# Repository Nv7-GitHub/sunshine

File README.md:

# Sunshine Combat Robot
This is the code for a 1lb melty-brain combat robot. This is a combat robot whose body spins and the wheel speeds are modulated while spinning for translation. There are 3 main components to this robot:

- Robot brain (sunshine_brain): ESP32-S3, which reads the sensors, does the processing, and sends the telemetry via ESP-now to the receiver and receives motion commands and safety-related commands (e.g. enable, disable, etc.)
- Receiver (sunshine_receiver): ESP32-S3, which receives the telemetry and sends it to the host app as well as sends out telemetry commands from the host app
- Host app (sunshine_app): Graphs data, displays telemetry, saves logs to files, handles replay (has to interact with sunshine_brain code for this) and simulation

## Tech stack
All embedded code will be implemented via platform IO. The host app code will be Tauri with React for the frontend. For replay (explained below), the brain code that is above the IO layer has to be very encapsulated so that it can be called from the Tauri rust code.

## Replay
The core concept of this project is IO layers and replay. The core sensors: **time (precise)**, wheel eRPM, ESP-NOW RSSI, magnetometer reading, battery voltage, control inputs from the driver, and accelerometer readings are all sampled at 1kHz and logged via telemetry. 

All the brain code processes these inputs (which are below the IO layer) and runs code that affects the **state**. The state is every variable that changes over time as a result of previous inputs. This should just be the external and internal states of any filters being used. 

The telemetry packets are sent out at 50 Hz, so each packet should include two state snapshots — one at the start of the packet and one at its midpoint (the 10th of its 20 samples), giving the real state at 100 Hz — and then the 20 IO layer samples that happened since the start state. The two states let the host both initialize the filters and double-check the replay against the real state twice per packet. This will minimize data usage because the host app can simply receive the state to initialize the filters and then run replay from there on. In the log files, the real state is likewise logged at 100 Hz (two snapshots per 50 Hz frame; theoretically you could even do it once but I want to be able to always have something to double-check the replay against and/or a way to handle changed code since you collected the telemetry) and the data below the IO layer is logged at the full 1kHz. Variables are NOT logged — they are a pure function of state + inputs, so the host always recomputes them (both the real and replayed versions).

The replay should use the ACTUAL robot code and just feed it a different source of IO layers instead of the raw sensors. So if you make a code change, you could re-run the code using the logged telemetry data and see if it fixes a bug that is occurring, for example.

This IO layer concept is important because it lets you implement simulation, where instead of having the receiver managing state you just implement a basic simulation of the motors and how it affects the sensors in an ideal world and then you can simulate the robot fully on the computer, once again just feeding the simulated sensor data into the IO layer.

In addition to the **state** and **inputs** (data below the IO layer) you also have the **variables** - data that is calculated from the state or inputs without any historical components. This is also logged at 50 Hz, but never sent over telemetry, just logged by the host app. This is once again so that if code changes occur you don't lose the data that was produced by the old code, which is necessary for determining if changes actually led to fixes. 

Replay is designed with AI assistance in mind. Develop Claude skills to aid with debugging code with validation via replay and simulation in parallel to this. Design everything with debugging and ugpradeability in mind. Changing what's in the state, what the inputs are, etc. should be easy and backwards-compatible (so old log data should still be usable). Adding a new variable (especially to the state and variables, which I anticipate changing a lot) should be very easy and well documented for future AI sessions along with the codebase in general.

## Robot brain

The robot brain has the two components mentioned before: below the IO layer, and above the IO layer. Everything above the IO layer has to be able to be run both on the host computer as well as the robot, so it should never interact with hardware directly and should be able to easily be compiled and run on a variety of host computer platforms. For below the IO layer, here is the hardware map:

## Hardware map
IMU is an ADXL375, 11mm from the center of the robot (this is important for calculating ang vel from the centripetal accel). The IMU is rotated 45 degrees so it saturates less.
- IO8: IMU_INT1
- IO9: IMU_INT2
- IO10: IMU_CS
- IO11: IMU_MOSI
- IO12: IMU_SCK
- IO13: IMU_MISO

Mag is LIS3MDL
- IO14: MAG_DRDY
- IO15: MAG_MOSI
- IO16: MAG_SCK
- IO17: MAG_MISO
- IO18: MAG_CS
- IO21: MAG_INT

There is an LED connected to IO38 that can be PWMed. It's connected to the gate of a low side switch so you drive it high to turn on the LEDs.

IO7 is connected with a voltage divider (2kohm high, one kohm low) to the battery positive terminal

IO4 is the signal pin of the left wheel ESC (S1), IO5 is for the right wheel ESC (S2). Use bidirectional DShot 600.

USB is connected, so you can use USB for debugging info

## Core splitting
There are 3 overall tasks running on the brain: telemetry, navigation, and control. 

### Telemetry
Telemetry should be running on the ESP32 core that is meant for telemetry. The data is getting sent out at a fixed 50 Hz and should be received from the transmitter at 500 Hz. This core should receive state (the history, or maybe it buffers the history itself but as explained earlier in each packet there's the state and then the 50 subsequent inputs). This core also uses the RSSI from the receiver and sends it over to the control core as this is one of the inputs. The receiver and transmitter should be configured to send at the absolute max strength, and the transmitter should be sending without waiting for acknowledgement or anything. For the telemetry it should be robust since any missing data will mess up replay, so determine a protocol that is able to do that without causing congestion so the packets with RSSI and control inputs can be sent at the 500 Hz. This is in a very RF noisy environment so account for that appropriately.

IMPORTANT: When the robot is disabled in the host app, it HAS to disable in real life. This is a strict requirement as it is critical to safety.

### Navigation
Navigation is the 1kHz sensor read and filter update loop. All the sensors can be read at 1kHz or faster (make sure to configure correctly) and all are connected via SPI so it should be fast. The filter is as follows:
- The accelerometer data is used to determine angular velocity. When being transmitted, this is an int16
- The magnetometer data goes through a butterworth filter with a cutoff roughly in the range of what Earth's magnetic field should be oscillating at. Calculate the minimum speed needed before zero DC leaks through and set that as the minimum speed to use this sensor, as there will be a lot of DC offset due to current draw from the ESC and various metallic objects. The raw reading is also an int16 for telemetry. The filter will be part of the state (and needs appropriate history). 
- The wheel ERPM is not going to be used for anything navigation-related. However, it can be used for torque-limiting and for looking at things like wheel slip in the logged data after. Log this as a float16.
- The RSSI is from the actual ESP-NOW receiving data. This is an int8. This is eventually going to be worked into the filter but I think the shape of it's curve depends on antenna stuff so I will collect some data not using it initially and try to analyze it before incorporating it into anything. 
- The host computer sends x, y, theta, and throttle. X/Y/Theta are all int8 and throttle is uint8. 
- The battery voltage can be represented as a int8, relative to 7.6V (the robot is 2S). The range needs to go to 5.0V and be symmetrical.
- Put the applied DShot signals into the inputs too, but quantize down to uint8 for each since I just want to see the overall shape at 1kHz, it is never going to be used anywhere.
- Time should be of the necessary precision to be accurate down to a decimal OF the control loop (so since the loop is at 1kHz, it should be accurate to ten-thousandths of a second) which means a uint32 is needed.

Make sure to consider endian-ness correctly for telemetry or use some protocol.

The overall Kalman filter will use the magnetometer as an absolute reference (since with the DC filtered out from the butterworth it should actually represent absolute position), the accelerometer gives velocity for the kalman filter, and eventually the RSSI will either give velocity or position but that is to be determined. 

The theta control defines an offset from the absolute position from the magnetometer. That way the driver can rotate the zero heading reference. 

The kalman filter will need to be tuned somewhat. Develop necessary code (this will probably happen during bringup) and include instructions to tune it. 

### Control
Control also happens in the same 1kHz loop. It is CRITICAL that this tight 1kHz loop does not overrun, and I should know about it when it is happening. The inputs include precise time so the host app should be receiving this, and of course loop overruns should be included in the USB output along with any initialization errors for the sensors. Make sure to have a distinct LED pattern if there are initialization errors too with the sensors, since usually I won't have USB connected during init so I would connect USB once I see that pattern (so the error should be continuously printed). 

During control, the LED has to be turned on from -3 deg to +3 deg (of course relative to the driver-controlled zero heading). 

The X and Y controls will be used for translational control. For the translational drift, use triangle waves in a portion of the rotation such that it can drive. The amplitude of the wave should depend on the magnitude of the X/Y control. Write a document on how to tune this (what to change and how that will affect the motion and what I should look for). I am thinking of a triangle wave instead of the usual square because the melty should be traction limited and a triangle wave should limit slip. Maybe a trapezoidal wave instead of a triangle if that would be more optimal.

There are two modes of control. There is DISABLED, which is critical to safety and the host app will control this. Then there is TANK, where the robot is driven around like a traditional robot, so throttle controls forwards backwards and the x control (side-to-side) should determine turning. Y and theta are unused. Finally, there is MELTY where throttle controls target angular speed (for now open-loop), X is for side-to-side, Y is forwards backwards, and theta controls the offset. This is holonomic unlike the previous tank drive mode so you can of course mix the X and Y. In the app design mockup (included below) there is only ENABLED and DISABLED so this needs to be changed to have DISABLED, TANK, MELTY.

## Bringup
There is no way that the entire codebase can be put onto the device and everything will work, so bringup needs to occur where each specific function has to be individually tested. Design a clean way of doing this. Here are the levels of bringup:
1. Low-level sensors: Read the accelerometer, plot via USB, make sure that works, same for the magnetometer, voltage sensor. etc.
2. Low-level control: Test the bidirectional DShot and make sure everything spins up correctly
3. Telemetry link: Test the ESP-NOW connection between the brain and the receiver, including sending the inputs and receiving the RSSI data. At this point the host app has to get in the loop too, and I should be able to plot accel, rssi, etc.
4. Navigation tuning: The kalman filter and other parameters must be tuned so that the device can localize well. At this point I will use the tank mode to spin the robot, MELTY mode will still not be used.
5. Drift tuning: MELTY mode is finally enabled, heading control should be good (so the LED should be solid and still), and I can tune the drift profile

Make sure it is an easy process and write instructions.

# Receiver
The receiver is simply the other side of the link from the robot brain. It should receive the necessary info and send it via USB (it is an ESP32-S3 so should have plenty of bandwidth) to the host app and send data. The accompanying protocols must be developed. 

# Host app
The UI mockup has been made:

## UI Mockup
Fetch this design file, read its readme, and implement the relevant aspects of the design. https://api.anthropic.com/v1/design/h/ER_Esv7z8Q_IkM8_wpP-5Q?open_file=Sunshine+Dashboard.html
Implement: Sunshine Dashboard.html

Note that this mockup has some unnecesary info plotted on top (e.g. CPU usage doesn't make sense, but seeing the bandwidth over the connection or the RSSI would be useful up there), and the variables are fully made up. Instead of ENABLE DISABLE there should be DISABLE, TANK, MELTY. In addition to x-y and throttle there is also the theta control. The current keybinds are:
W/S for Y, A/D for X, left/right arrow for theta, and up/down arrow for throttle (where throttle adds up instead of being like when you let go it goes to zero). This should be HEAVILY low-pass filtered (even more than the current mockup) so that I can basically emulate having a controller by pulsing WASD and the left/right arrow keys.

The connections section of the UI doesn't make sense. Robot is 2S so of course adjust battery indicator colors accordingly. Get rid of the E-STOP button as that's the same as DISABLE. Inputs menu is unneeded. Retain the same graph controls but fix it because right now it's a little jerky and awkward (way too sensitive to the scroll). 

You should be able to do replay, simulation, and connect to the real robot through the UI. Implement that stuff into where the "CONNECTIONS" area is currently. For replay you would pick a log file, simulation just spins up a simulation, and connecting to the robot would connect to the receiver and then look at whether the receiver is connected and all. Error handling will need to be coordinated across all devices in the chain in a robust and extendable manner.

## Logging
The code needs to log a decent amount of data at 50 Hz (where each 50 Hz frame has those 20 inputs). Use binary so the file is small and of course design around the backwards compatibility aspect so that old files can be used with versions of the software that have new variables.

## Plotting
You should be able to plot both the actual 50 Hz data as well as your replayed data for the state variables (this applies when connected to the real robot as well as when replaying from a data file, in simulation it doesn't really make sense but they can probably just be the same thing but one is at 50 Hz). The only reason we replay even when connected to the real robot is so that we can see what's going on at 1kHz, so the replayed data should look like a high-resolution version of the 50 Hz data. Make sure to design the graphing UI such that it can handle the high density of points / quantize since of course rendering at 1kHz when you are showing a minute of data would probably cause lag issues, so consider that when implementing the graphing. 

## Inputs, State, and Variables
All things being plotted have their own units. You can already see this system well implemented in the mockup.

The inputs should all be plotted under the inputs dropdown. Most of the state (e.g. the kalman filter internal covariances, butterworth history) don't make sense to plot so only things like position, velocity, and the magnetometer data after the filter really make sense to plot.

Even though the control outputs are logged at 1kHz as part of the inputs, they will get re-calculated during replay and so there should be a way of viewing the new control outputs too. That's why even though during telemetry they are part of the inputs in the app graphing they should be part of the STATE since they have separate values received vs replayed. We basically have a Real State and a Replayed State which of course includes the 50 Hz things above but also the 1kHz wheel applied values.

The variables are only present in the replayed values, as they are never sent from the robot. Think of all important values. e.g. velocity calculated from the accelerometer would be a variable that should be plotted. All possibly useful info should be plottable.

The app has to call the actual C code to emulate the control and state estimation. This will require calling of C code from Rust. 

## Simulation
Use the basic electrical model of a brushed motor. (Back-EMF source, resistance, etc.). The KV of the motors is 1100KV (this should be an easily editable constant though). I don't know the exact resistance but lets say each phase is 75mohm. The battery is a 2S 650mah 120C LiPo. Don't model battery draining but model internal resistance using like the supply current derived from the stator current in the motor, pick a reasonable internal resistance for a battery with these specs. For the magnetomer, just do ideal earth's magnetic field, same for accelerometer. here are some more physical parameters you need:
- Wheel Diameter: 44mm
- The wheels are 81mm apart (so radius from center is 40.5mm). 
- The MoI of the robot is 1213859.17531 g-mm^2
- Wheel MoI is 6407.44019 g-mm^2
Use metric for everything.

I believe the max body RPM is somewhere around 4,000, you should double check this to ensure I gave you the right-specs.

# General Notes
Everything should be implemented robustly. If everything is connected and setup but then I unplug and replug the receiver, the host app should handle that gracefully and make a new log file. There also should be an easy way to disable logging from the host app. If the robot momentarily loses power or disconnects and then reconnects the host app and receiver should handle this gracefully. The disabled aspect is critical to safety. The code should be very well documented (in MD files) such that future AI sessions can read an info document and know what files to edit. There should be instructions for tuning meant for humans. Also make it easy to label log files (e.g. during comp it should be based on match, but always include date and stuff)

IMPLEMENT SKILLS TO AID WITH DEBUGGING!

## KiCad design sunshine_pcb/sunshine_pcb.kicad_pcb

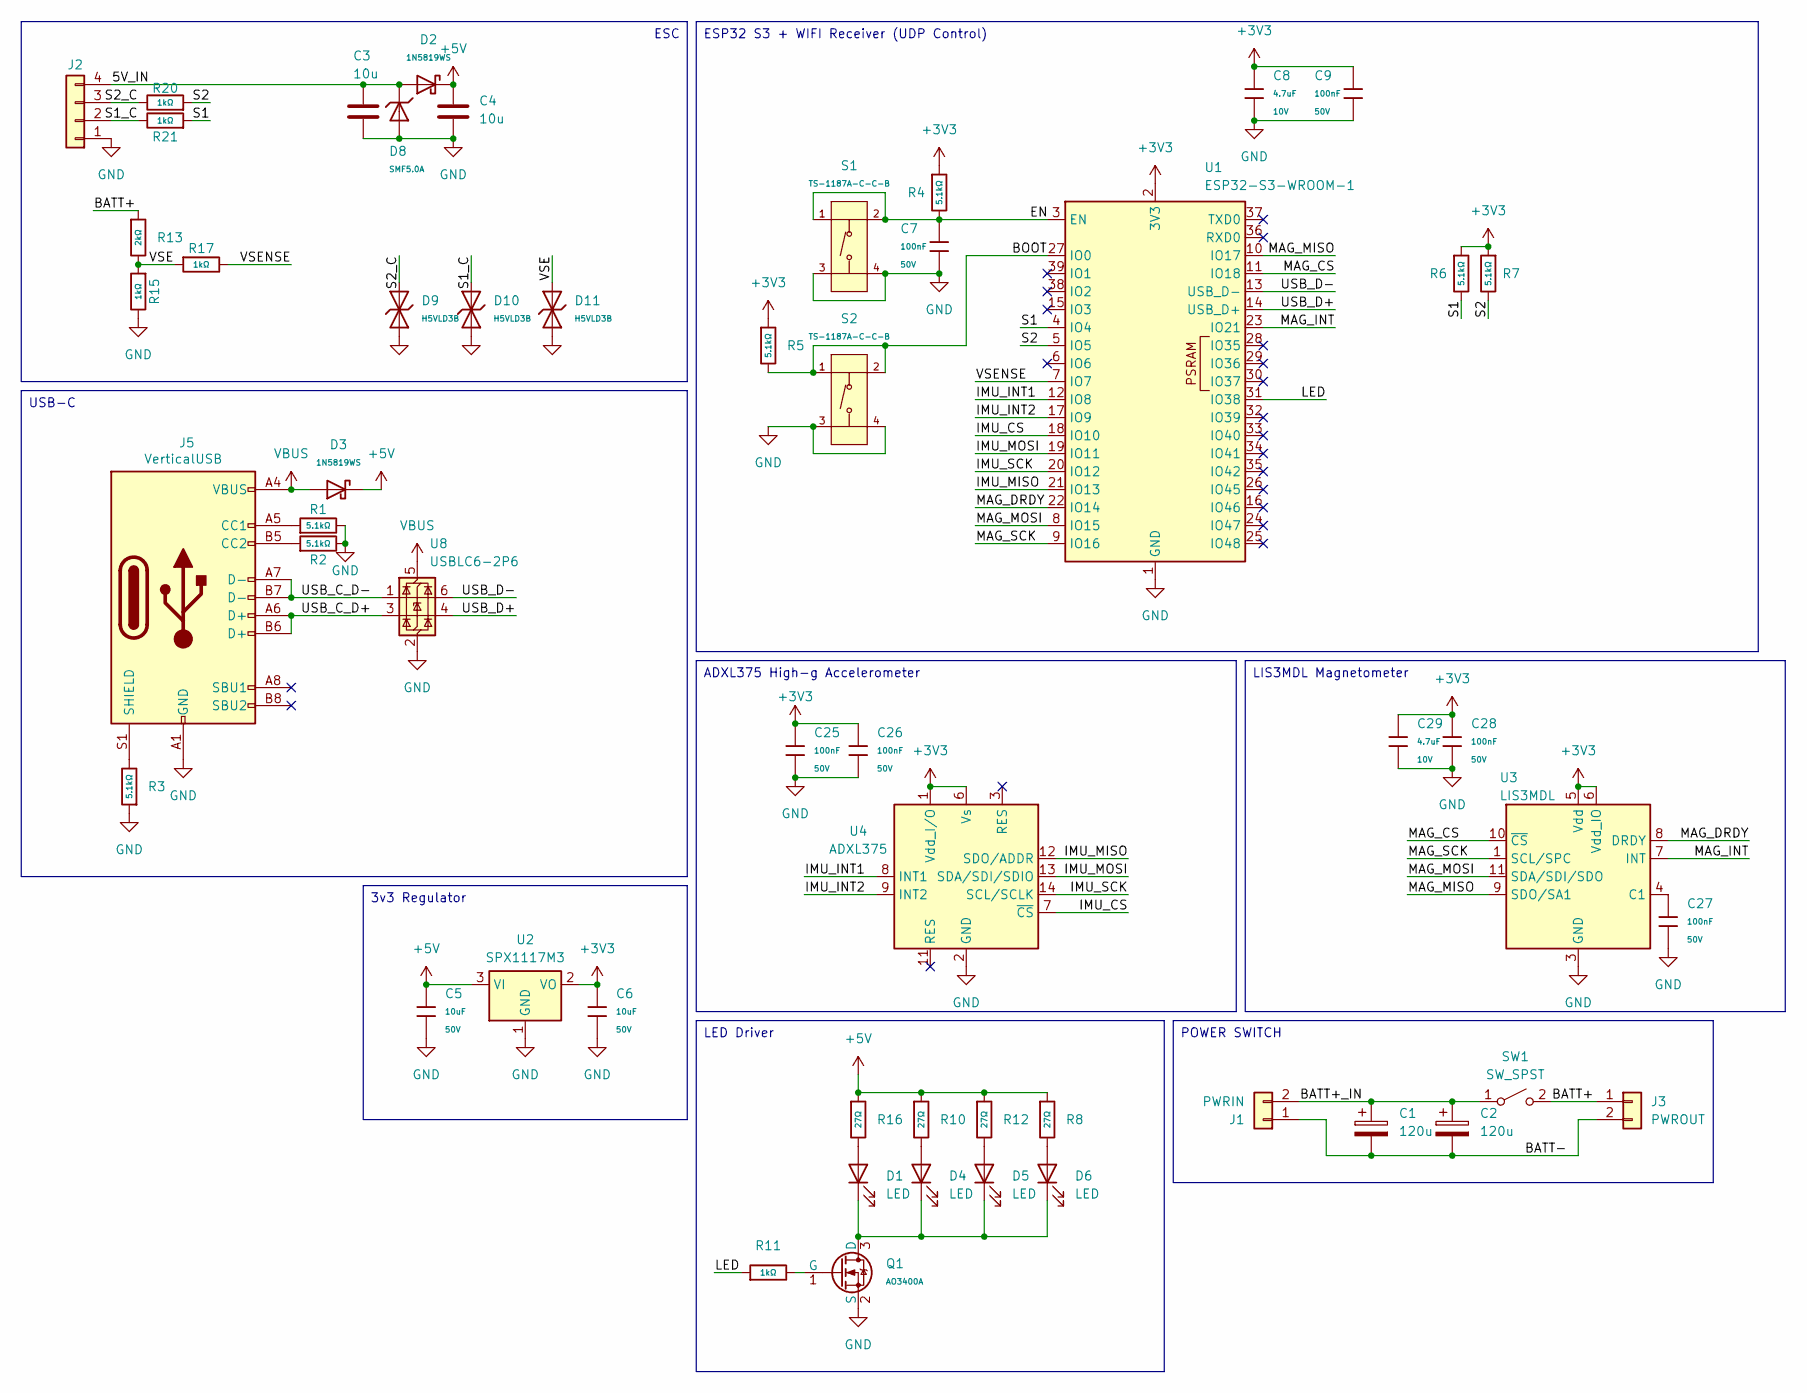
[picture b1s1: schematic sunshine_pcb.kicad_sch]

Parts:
C1, C2: 120u; CP_Radial_D6.3mm_P2.50mm
C3, C4: 10u; C_1210_3225Metric; LCSC C437431
C5, C6: 10uF; C_0805; Voltage Rated 50V; Tolerance ±10%; Part GRM21BR61H106KE43L; LCSC C440198
C7, C9, C25, C26, C27, C28: 100nF; C_0402; Voltage Rated 50V; Tolerance ±10%; Part CL05B104KB54PNC; LCSC C307331
C8, C29: 4.7uF; C_0402; Voltage Rated 10V; Tolerance ±20%; Part CL05A475MP5NRNC; LCSC C23733
D1, D4, D5, D6: LED; LED_PLCC_2835; LCSC C2843876
D2, D3: 1N5819WS; D_SOD-323; Forward Voltage (Vf@If) 600mV@1A; Reverse Voltage (Vr) 40V; Part 1N5819WS; LCSC C191023
D8: SMF5.0A; D_SOD-123FL; Part SMF5.0A; LCSC C19077497
D9, D10, D11: H5VLD3B; D_SOD-323; Part H5VLD3B; LCSC C20615805
J1: PWRIN; AMASS_XT30PW-M_1x02_P2.50mm_Horizontal
J2: Conn_01x04; SolderConnector4P; LCSC C122413
J3: PWROUT; SolderWire-1.5sqmm_1x02_P6mm_D1.7mm_OD3mm
J5: VerticalUSB; CONN_GT-USB-7055A_GSW
Q1: AO3400A; Q_SOT-23; Part AO3400A; LCSC C20917
R1, R2, R3, R4, R5, R6, R7: 5.1kΩ; R_0402; Overload Voltage (Max) 50V; Tolerance ±1%; Part 0402WGF5101TCE; LCSC C25905
R8, R10, R12, R16: 27Ω; R_0805; Overload Voltage (Max) 150V; Tolerance ±1%; Part 0805W8F270JT5E; LCSC C17594
R11, R15, R17, R20, R21: 1kΩ; R_0402; Overload Voltage (Max) 50V; Tolerance ±1%; Part 0402WGF1001TCE; LCSC C11702
R13: 2kΩ; R_0402; Overload Voltage (Max) 50V; Tolerance ±1%; Part 0402WGF2001TCE; LCSC C4109
S1, S2: TS-1187A-C-C-B; SW-SMD_4P-L5.1-W5.1-P3.70-LS6.5-TL-2; Voltage Rating (Dc) 12V; Part TS-1187A-B-A-B; LCSC C318889
SW1: SW_SPST; screw_switch
U1: ESP32-S3-WROOM-1; LCSC C2913202
U2: SPX1117M3; SOT-223-3_TabPin2; LCSC C6862
U3: LIS3MDL; LGA-12_2x2mm_P0.5mm; LCSC C478483
U4: ADXL375; LGA-14_3x5mm_P0.8mm_LayoutBorder1x6y; LCSC C481898
U8: USBLC6-2P6; SOT-666; LCSC C15999

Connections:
+3V3: C6.1, C8.1, C9.1, C25.1, C26.1, C28.1, C29.1, R4.1, R5.1, R6.1, R7.1, U1.2 (3V3), U2.2 (VO), U3.5 (Vdd), U3.6 (Vdd_IO), U4.1 (Vdd_I/O), U4.6 (Vs)
+5V: C4.1, C5.1, D2.1, D3.1, R8.1, R10.1, R12.1, R16.1, U2.3 (VI)
/5V_IN: C3.1, D2.2, D8.1, J2.4
/BATT+: J3.1, R13.1, SW1.2 (B)
/BATT+_IN: C1.1, C2.1, J1.2, SW1.1 (A)
/BATT-: C1.2, C2.2, J1.1, J3.2
/BOOT: R5.2, S2.1 (A), S2.2 (B), U1.27 (IO0)
/EN: C7.1, R4.2, S1.1 (A), S1.2 (B), U1.3 (EN)
/IMU_CS: U1.18 (IO10), U4.7 (~CS)
/IMU_INT1: U1.12 (IO8), U4.8 (INT1)
/IMU_INT2: U1.17 (IO9), U4.9 (INT2)
/IMU_MISO: U1.21 (IO13), U4.12 (SDO/ADDR)
/IMU_MOSI: U1.19 (IO11), U4.13 (SDA/SDI/SDIO)
/IMU_SCK: U1.20 (IO12), U4.14 (SCL/SCLK)
/LED: R11.1, U1.31 (IO38)
/MAG_CS: U1.11 (IO18), U3.10 (~CS)
/MAG_DRDY: U1.22 (IO14), U3.8 (DRDY)
/MAG_INT: U1.23 (IO21), U3.7 (INT)
/MAG_MISO: U1.10 (IO17), U3.9 (SDO/SA1)
/MAG_MOSI: U1.8 (IO15), U3.11 (SDA/SDI/SDO)
/MAG_SCK: U1.9 (IO16), U3.1 (SCL/SPC)
/S1: R6.2, R21.1, U1.4 (IO4)
/S1_C: D10.2, J2.2, R21.2
/S2: R7.2, R20.1, U1.5 (IO5)
/S2_C: D9.2, J2.3, R20.2
/USB_C_D+: J5.A6 (D+), J5.B6 (D+), U8.3 (I/O2)
/USB_C_D-: J5.A7 (D-), J5.B7 (D-), U8.1 (I/O1)
/USB_D+: U1.14 (USB_D+), U8.4 (I/O2)
/USB_D-: U1.13 (USB_D-), U8.6 (I/O1)
/VSE: D11.2, R13.2, R15.1, R17.1
/VSENSE: R17.2, U1.7 (IO7)
GND: C3.2, C4.2, C5.2, C6.2, C7.2, C8.2, C9.2, C25.2, C26.2, C27.2, C28.2, C29.2, D8.2, D9.1, D10.1, D11.1, J2.1, J5.A1 (GND), J5.A12 (GND), J5.B1 (GND), J5.B12 (GND), Q1.2 (S), R1.2, R2.2, R3.1, R15.2, S1.3 (C), S1.4 (D), S2.3 (C), S2.4 (D), U1.1 (GND), U1.40 (GND), U1.41 (GND), U2.1 (GND), U3.2 (GND), U3.3 (GND), U3.12 (GND), U4.2 (GND), U4.4 (GND), U4.5 (GND), U8.2 (GND)
unnamed: D1.2 (A), R16.2
unnamed: D1.1 (K), D4.1 (K), D5.1 (K), D6.1 (K), Q1.3 (D)
unnamed: D4.2 (A), R10.2
unnamed: D5.2 (A), R12.2
unnamed: D6.2 (A), R8.2
unnamed: J5.A5 (CC1), R1.1
unnamed: J5.B5 (CC2), R2.1
unnamed: J5.S1 (SHIELD), R3.2
unnamed: Q1.1 (G), R11.2
unnamed: C27.1, U3.4 (C1)
VBUS: D3.2, J5.A4 (VBUS), J5.A9 (VBUS), J5.B4 (VBUS), J5.B9 (VBUS), U8.5 (VBUS)

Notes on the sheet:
ADXL375 High-g Accelerometer
ESC
LIS3MDL Magnetometer
LED Driver
3v3 Regulator
POWER SWITCH
USB-C
ESP32 S3 + WIFI Receiver (UDP Control)

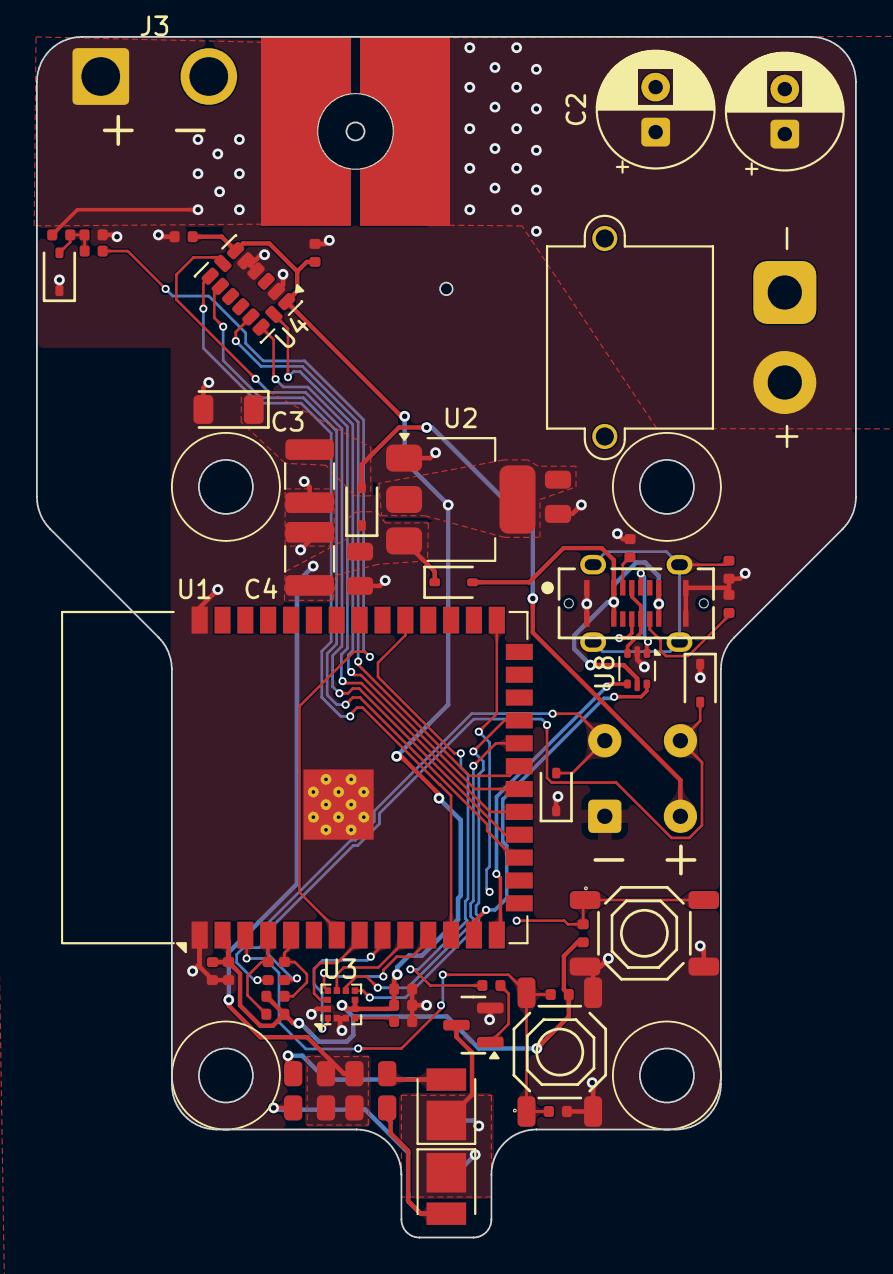
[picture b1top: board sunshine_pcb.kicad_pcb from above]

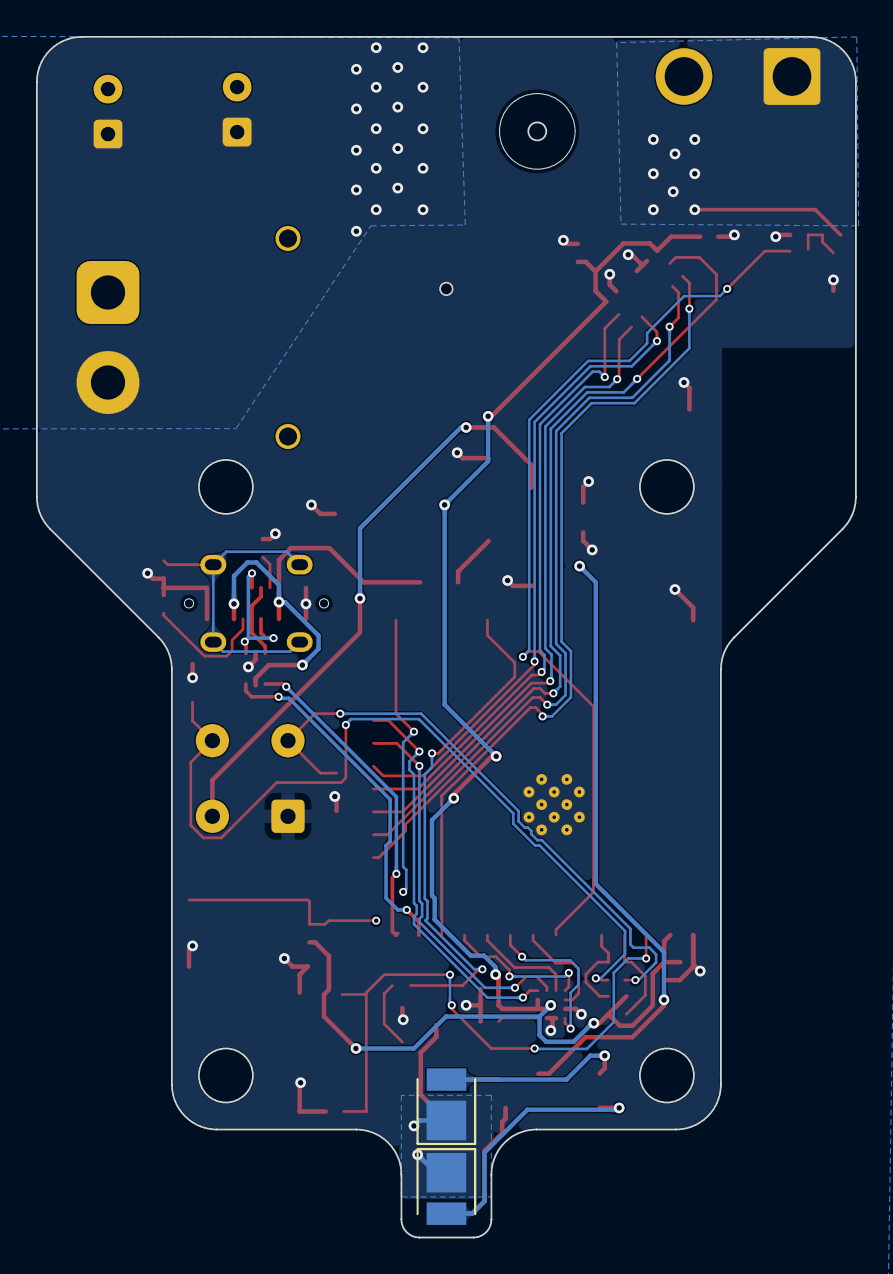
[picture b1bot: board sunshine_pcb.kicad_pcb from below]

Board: 4 copper layers, 45.5 x 66.7 mm, 54 parts (2 on the bottom side), 43 nets.

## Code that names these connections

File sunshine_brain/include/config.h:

#pragma once
#include <stdint.h>

// ── SPI pins
// ────────────────────────────────────────────────────────────────── FSPI →
// ADXL375
#define PIN_ADXL_CS 10
#define PIN_ADXL_MOSI 11
#define PIN_ADXL_SCK 12
#define PIN_ADXL_MISO 13
// INT pins (not used in polled mode, reserved)
#define PIN_ADXL_INT1 8
#define PIN_ADXL_INT2 9

// HSPI → LIS3MDL
#define PIN_MAG_CS 18
#define PIN_MAG_MOSI 15
#define PIN_MAG_SCK 16
#define PIN_MAG_MISO 17
#define PIN_MAG_DRDY 14
#define PIN_MAG_INT 21

// ── DShot
// ─────────────────────────────────────────────────────────────────────
#define PIN_DSHOT_LEFT 4   // S1
#define PIN_DSHOT_RIGHT 5  // S2
// AM32 2.x auto-detects BDSHOT from the inverted CRC — no configurator setting
// needed.
#define DSHOT_BIDIRECTIONAL 1

// ── Battery ADC
// ─────────────────────────────────────────────────────────────── ADC1_CH7 =
// GPIO7, connected to battery voltage divider (R_high=2k, R_low=1k)
#define PIN_BATT_ADC 7
// V = adc_raw * (3.3/4095) * (R_high+R_low)/R_low = adc_raw * (3.3/4095) * 3.0
static constexpr float BATT_ADC_SCALE = (3.3f / 4095.0f) * 3.0f;
// Battery low-pass cutoff. The raw ADC carries a strong ~50 Hz (2×-spin) EMI
// tone
// (~±100 mV) that swamps the 20 mV telemetry resolution and makes batt_voltage
// unusable. A single-pole IIR at this cutoff rejects it (~10× at 50 Hz) while
// still passing real current-draw sag (tens–hundreds of ms). Raise for snappier
// sag response, lower for a smoother trace. (Oversampling within the 1 kHz tick
// would NOT help — the noise is a slow spin-synchronous tone, not fast ADC
// noise.)
static constexpr float BATT_LP_HZ = 6.0f;

// ── LED
// ───────────────────────────────────────────────────────────────────────
#define PIN_LED 38
// Duty levels for analogWrite (8-bit, 0..255).
// Armed brightness: the MELTY heading flash and the TANK solid-on "armed"
// indicator. ALWAYS full brightness — the flash is only shown while spinning,
// where it must be visible in daylight, so it's never dimmed by bringup level.
#define LED_DUTY_ACTIVE 255
// DISABLED "breathe" and the sensor-init-error blink: a dim "board alive"
// indicator. Kept low at all times (the robot is stationary on a desk when
// these show), independent of bringup level. Tune to taste.
#define LED_DUTY_IDLE 40

// ── Timing
// ────────────────────────────────────────────────────────────────────
static constexpr uint32_t LOOP_INTERVAL_US = 1000;  // 1 kHz
static constexpr uint32_t CTRL_WATCHDOG_MS = 500;   // no ctrl → DISABLED

// ── Motor direction
// ─────────────────────────────────────────────────────────── Set to true to
// invert a motor's DShot output (mirrors forward↔reverse around DSHOT_NEUTRAL).
// Use this when wiring or AM32 direction can't be changed. In MELTY mode with
// no translation input, both motors spinning "forward" should produce CCW body
// rotation (viewed from above). If the robot spins CW, flip both. If only one
// motor spins the wrong way, flip that one. See BRINGUP.md Level 2 for the
// verification procedure.
static constexpr bool MOTOR_LEFT_INVERT = false;
static constexpr bool MOTOR_RIGHT_INVERT = true;

// ── ESP-NOW
// ───────────────────────────────────────────────────────────────────
static constexpr uint8_t ESPNOW_CHANNEL = 1;
// Receiver MAC — AUTO-LEARNED at runtime from the receiver's control packets
// (telemetry.cpp), so this does NOT need to be filled in. It is only the
// pre-pairing bootstrap: broadcast (FF:..) until the first control packet
// arrives, after which telemetry switches to UNICAST to the learned MAC (→ MAC
// ACK + hardware retransmit = no lost frames). Leave as broadcast unless you
// want to hard-pin a specific receiver.
static const uint8_t RECEIVER_MAC[6] = {0x44, 0x1B, 0xF6, 0xD6, 0x46, 0x50};

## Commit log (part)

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2025-12-30 Make RC PWM reader
2025-12-30 Fix printing
2025-12-30 Add kicad project
2025-12-31 Start designing PCB, make the code work (on chan B)
2025-12-31 Get it working (needed second core)
2025-12-31 Clean up code
2025-12-31 Bring in DShot
2025-12-31 Try to make it work (failed)
2026-01-01 Do layout
2026-01-01 Add some protection
2026-01-23 Re-do schematic for ESP32
2026-01-23 Re-layout board for ESP32
2026-01-23 Fix issue with mosfet
2026-01-24 Route PCB
2026-02-05 Update PCB
2026-02-09 Re-design PCB to not interact with VDC
2026-02-16 Change connector to be soldered
2026-02-16 Add voltage sense line
2026-02-16 Use brighter LED
2026-05-16 Update design for new switch
2026-05-16 Re-layout PCB
2026-05-16 Fix switch
2026-05-16 Add teardrops
2026-05-16 Fix the extension, round the other tracks
2026-05-16 Fix hole clearance
2026-05-26 Get rid of old code
2026-05-26 Initial PRD
2026-05-26 Add simulation info
2026-05-26 Update IMU mounting info
2026-05-26 Fix design link
2026-05-27 prompts
2026-05-27 CMake gitignore
2026-05-27 Claude stuff
2026-05-27 I hate DS_Store
2026-05-27 feat(brain): PlatformIO project scaffold, bringup gates, sunshine_core lib
2026-05-27 fix(brain): ring buffer drop-on-full to avoid write/read race, add trivially_copyable assert
2026-05-27 fix(brain): nav loop overrun flag per-tick, t_next resync before printf, batt clamp -128
2026-05-27 fix(brain): check xTaskCreatePinnedToCore return values, halt on failure
2026-05-27 Update gitignore
2026-05-27 feat(receiver): add PlatformIO project scaffold and config
2026-05-28 pnpm
2026-05-28 More plans
2026-05-28 No worktrees
2026-05-28 Fix so many bugs
2026-05-29 Fix many more bugs
2026-05-29 Even more bug fixes?
2026-05-29 More bugfixes
2026-05-29 More fixes!
2026-05-29 Fix zooming
2026-05-29 Codex cooking
2026-05-29 Codex finds bugs
2026-05-29 Missing physics info
2026-05-29 Fix simulator physics
2026-05-30 Fix logging
2026-05-30 Fix replay bugs, normalize joysticks
2026-06-06 Bugfixes
2026-06-06 Update schematic
2026-06-06 Update docs
2026-06-06 Fix brightness
2026-06-06 Get DShot working better but not fully working
2026-06-06 Config receiver MAC
2026-06-07 Bugfixes to DShot
2026-06-07 Ugh i hate dshot
2026-06-07 Fix symlink
2026-06-07 DShot bidirectional telemetry decode fix + N16R8 board config
    - Decode GCR telemetry at 4/5 of the command bit period; real 3-bit runs
    were quantizing to 2 bits, the cause of the ~90% CRC-fail rate
    - Accept CRC-valid 0xFFF as the zero-eRPM "motor stopped" sentinel instead
    of tallying it as a CRC failure
    - Force an ESC reset with a brief LOW pulse in dshot_init so a warm brain
    reset re-arms AM32 without a physical power-cycle
2026-06-07 Receiver: onboard RGB status LED for link/liveness state
    Add a non-blocking WS2812 status driver (led_status.{h,cpp}) and wire it
    into the bridge:
    - white breathe = boot/idle, red blink = fatal ESP-NOW init error
    - red breathe = no brain, amber = brain up but host silent, green = both live
    - brief flash per forwarded telemetry frame as an activity blip
    - millis-based breathing, writes throttled to ~60 Hz; error blink now ticks
2026-06-07 Seed replay from transmitted filter state; disconnect UI + fixes
    Replay seeding (the core fix):
    - brain: snapshot filter state BEFORE sunshine_step and push that with the
    frame, so telemetry carries "state at start of frame" as replay expects
    (pairing inputs with post-step state seeded replay one sample ahead)
    - pipeline: seed replay_state from the first ingested frame's state, re-armed
    on brain reconnect; also seed offline replay from the first logged state.
2026-06-07 1 kHz loop timing: faster sensor SPI, DShot600, profiling + replay polish
    Brain loop budget:
    - adxl375: bypass Adafruit driver on the hot path, burst-read DATAX0..DATAZ1
    at 5 MHz SPI_MODE3 (driver hardcodes 1 MHz, ~100 µs/read)
    - lis3mdl: raise SPI clock to 5 MHz (~5× shorter transfer)
    - dshot: DSHOT300 → DSHOT600, halving TX frame + blocking wait time
    - nav_control: per-section µs PROF print (adxl/mag/batt/ctrl/step/dshot/rest +
2026-06-07 Fix led
2026-06-07 App fixes
2026-06-07 Fix looptime growing
2026-06-07 Fix scaling for dshot
2026-06-07 Bringup L4: let TANK mode drive motors for nav tuning
    Split the old "zero dshot at levels 3-4" guard:
    - Level 3 (telemetry bringup) keeps FORCE_DSHOT_ZERO — no motion at all
    - Level 4 (nav tuning) gets TANK_ONLY_OUTPUT: only TANK mode drives so you can
    spin the robot to tune the Kalman/derot filters; DISABLED and MELTY stay
    zeroed (MELTY isn't tuned until Level 5). Production (L0) still drives all modes
    - update bringup.h level legend and BRINGUP.md Level 4 setup notes (props off)
2026-06-07 Better idle LED
2026-06-10 Fix app controls
2026-06-11 Fix controls bug
2026-06-11 Claude is stupid
2026-06-11 Revert sorta
2026-06-11 Add error messages, fix controls
2026-06-11 Claude wanted to change a comment
2026-06-13 Bugfixes + app logo
2026-06-13 Recompile tech
2026-06-13 Fix simulation
2026-06-13 Fix cleanup between sources
2026-06-13 Fix dshot simulation
2026-06-14 dshot: sanitise corrupt eRPM telemetry decodes
    Bidirectional-DShot frames carry only a weak 4-bit GCR checksum, so a few
    percent decode to garbage — implausibly low values or tiny periods that yield
    ~6e7 eRPM and overflow the float16 telemetry field to +inf (the dropouts and
    inf spikes in recorded logs).
    Add a three-stage ErpmFilter per motor, exploiting the flywheel's high inertia
    (true eRPM changes slowly, so any large single-sample jump is a decode error):
2026-06-14 lis3mdl: 1000 Hz ODR so the 1 kHz loop reads a fresh mag sample each tick
    At 155 Hz the same conversion was re-read ~6× per tick while est_theta
    advanced 20–40° at high spin, smearing the synchronous derotation (|derot|
    collapsed 25→6 µT above ~500 RPM). 1000 Hz (LP mode + FAST_ODR) delivers one
    fresh sample per tick — exactly what the fs=1000 Hz LP4 derot filter assumes;
    LP-mode per-sample noise is dominated out by that filter's heavy averaging.
    Keep using setDataRate alone (it sets LP + FAST_ODR); a separate
2026-06-16 Fix VSENSE net
2026-06-19 Fix app on disconnect event
2026-06-21 Replay source bugfixes
2026-06-21 50 Hz telemetry over ESP-NOW v2 (20 inputs/packet) + offline replay harness
    Telemetry frame (brain + receiver + host, kept in sync):
    - ESP-NOW v2 (IDF >= 5.4, pioarduino 55.03.38) lifts the 250 B payload cap to
    1490, so send the README-intended 50 Hz frame: one packet per 20 inputs
    (643 B) instead of 6 inputs/~167 Hz. ~3.3× fewer packets relieves the ring
    backpressure that was dropping ~5% of 1 kHz inputs
    - brain telemetry.cpp: INPUTS_PER_FRAME 6→20, ring 32→64, static_assert frame
2026-06-21 100 Hz real state: dual state snapshot per frame, log format VER 3
    Telemetry/log now carry the real filter state twice per 50 Hz frame (at the
    first input and the midpoint), so the host has a 100 Hz ground-truth reference
    to re-anchor and validate replay against — per the README's revised design.
    Wire + log:
    - brain telemetry.cpp: write state_start at drain 0 and state_mid at the
    midpoint input; frame 643→703 B, ring layout updated
2026-06-22 core: open-loop mag tracking band-pass heading; fix MELTY precession
    Replace synchronous-demodulation derotation (derot_filter.c) with an open-loop
    magnetometer heading (mag_heading.c): a 2nd-order RBJ band-pass centred on the
    spin frequency (from kf_omega) isolates the Earth-field sine — its DC zero kills
    hard-iron + averaged ESC-current offset, and the skirt rejects the fs/6≈167 Hz
    LP-mode sampling tone a fixed filter can't. Bandwidth is a constant fraction of
    fc (Q=1.5 → half-BW ≈ 33% of spin) so the true spin stays in-band at any speed
2026-06-22 docs: align with open-loop mag-heading band-pass filter
    Update ARCHITECTURE/BRINGUP/DEBUGGING/FILTER_MATH/TUNING for the mag-heading
    redesign:
    - FILTER_MATH: rewrite the heading section — spin-tracking RBJ band-pass (DC
    zero kills hard-iron, peak tracks kf_omega, rejects the 167 Hz LP-sampling
    tone), constant-Q ±33% band, atan2 of the quadrature axes, and the soft-iron
    ellipse ±10° zero-mean (non-drifting) wobble
2026-06-22 core: fix mag band-pass false-lock; enlarge telemetry ring
    Mag heading (the real fix): centre the tracking band-pass on omega_from_accel
    (a direct accel measurement) instead of kf_omega. The band-pass output sets
    kf_theta, which feeds kf_omega back through the Kalman cross-covariance, so
    centring on kf_omega closes a loop whose per-tick coefficient modulation
    parametrically FALSE-LOCKS the recovered heading at half the true spin rate.
    omega_from_accel is loop-independent, breaking that loop; the accel's few-%
2026-06-22 telemetry: reliable unicast delivery (MAC ACK + retransmit) end-to-end
    Broadcast ESP-NOW has no ACK/retry, so any collision — including the
    half-duplex receiver being mid-control-TX — was a permanent lost frame and
    broke replay. Switch telemetry to UNICAST so the WiFi MAC ACKs and retransmits
    in hardware:
    - pairing: prefer a hard-coded RECEIVER_MAC (config.h) — deterministic, and we
    then reject control from any other MAC (multi-device arena). If left
2026-06-22 Add in MAC address
2026-06-22 telemetry: TX flow control + drop sends when the link is down
    Two robustness fixes on top of unicast telemetry, both preventing an ESP-NOW TX
    queue overflow (ESP_ERR_ESPNOW_NO_MEM) that would stall the ring drain:
    - One frame in flight at a time: wait on a tx_done_sem (given by the send
    callback) before the next esp_now_send, so the ESP-NOW TX queue can't back up
    when the ring bursts. Primed once at init; 50 ms fail-safe timeout, and a
    failed send gives the sem back immediately (no callback will fire).
2026-06-23 telemetry: two-stage assemble/send split; LED beacon survives high spin
    Telemetry: split into two Core-0 tasks decoupled by a frame FIFO (48 frames ≈
    1 s at 50 Hz):
    - Stage A (telemetry_task): drains the 1 kHz input ring and assembles whole
    frames, NEVER blocking on TX. RF congestion / unicast retries can no longer
    back up the input ring → fixes input loss under congestion. Link-down frames
    are dropped here (ring already drained).
2026-06-23 control: balanced bipolar MELTY drift wave; replay CSV adds eRPM + stored state
    MELTY translation: replace the asymmetric trapezoid() with a balanced bipolar
    drift_wave(). The + and - plateaus are now 180° apart with equal area and the
    ramps fill the rest of the cycle, so the differential is zero-mean and
    half-wave symmetric (wave(φ+π) == -wave(φ)) — no net torque bias that would
    skew the spin. Tuning:
    - DRIFT_PLATEAU_WIDTH (fraction per plateau) replaces DRIFT_PULSE_WIDTH +
